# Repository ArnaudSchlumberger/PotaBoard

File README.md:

# PotaBoard

This repository contains all the code, and PCB design files related to PotaBoard, a BLE-powered board kitchen garden.

It comes with capacitive-moisure sensor and BME280 compatibility for temperature and pressure measurements.

Used microcontroller : ATtiny1604 with Arduino Nano UPDI Programmer

BLE module : EMB1061.

All eletronics-related files are in 'Electronics - Extras' folder, and contains:
- Components Datasheets in 'Datasheets' folder
- Kicad project and related libraries in 'Kicad project' folder

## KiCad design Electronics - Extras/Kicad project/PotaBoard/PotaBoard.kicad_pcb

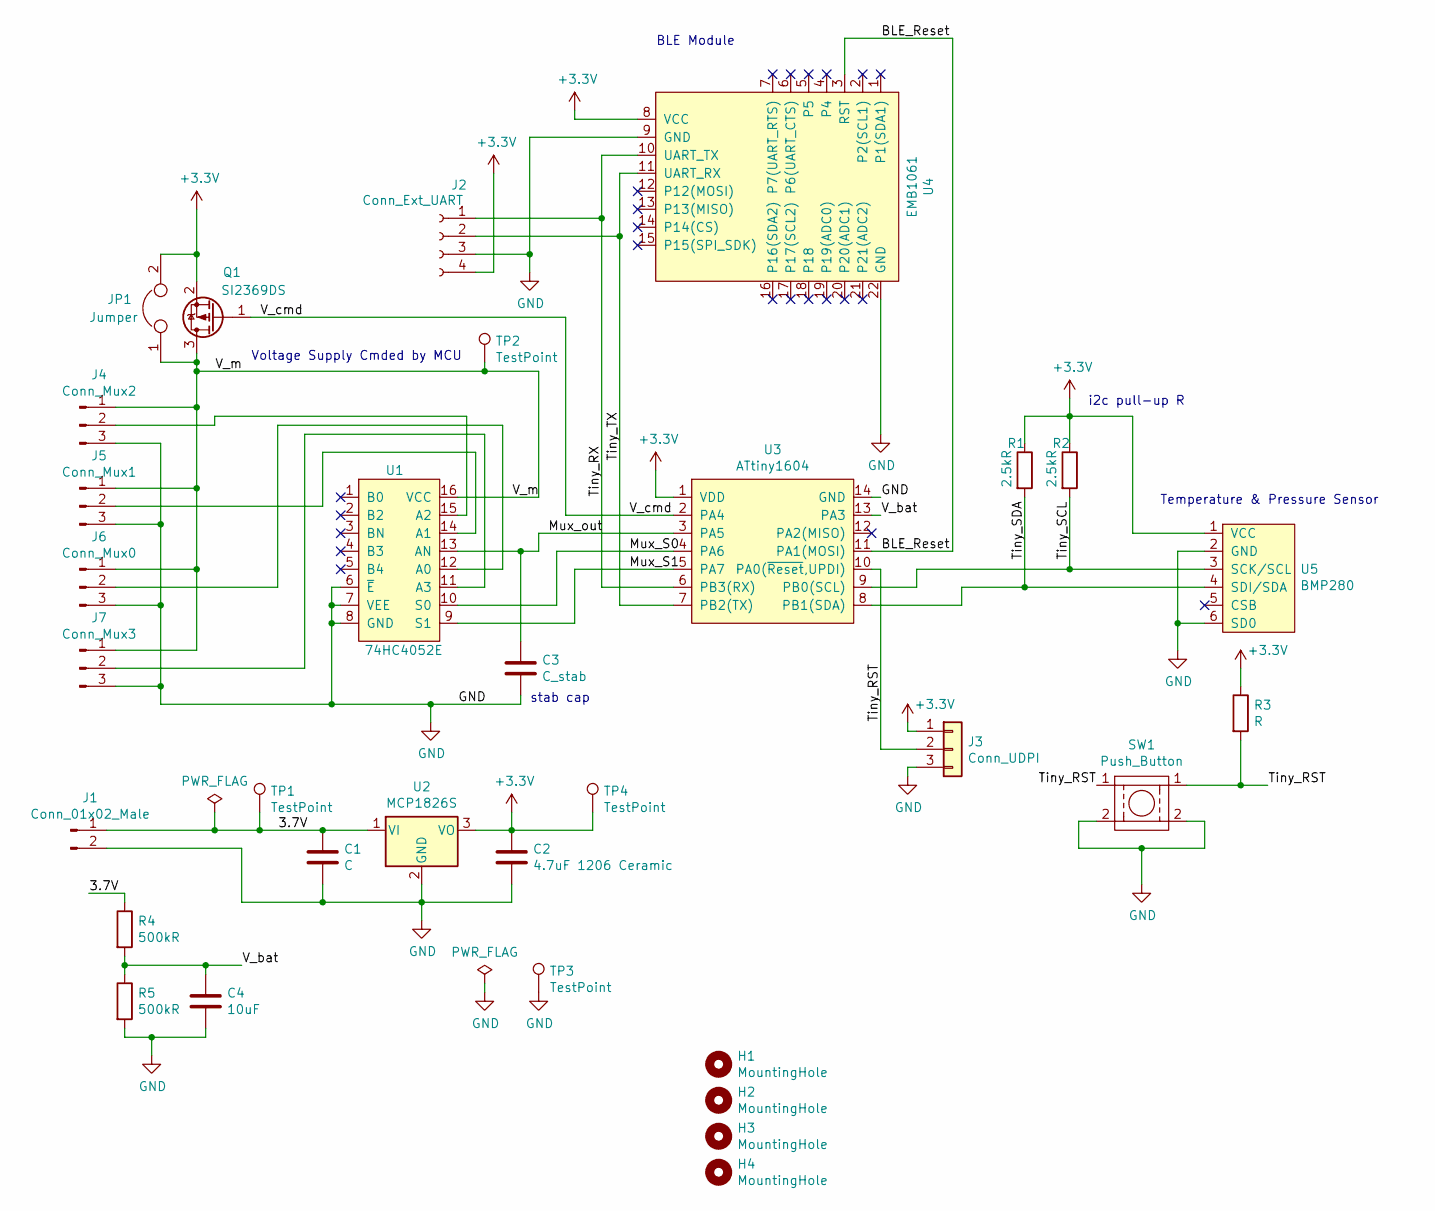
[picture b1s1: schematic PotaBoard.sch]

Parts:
C1: C; C_1206_3216Metric_Pad1.42x1.75mm_HandSolder
C2: 4.7uF 1206 Ceramic; C_1206_3216Metric_Pad1.42x1.75mm_HandSolder
C3: C_stab; C_1206_3216Metric_Pad1.42x1.75mm_HandSolder
C4: 10uF; C_1206_3216Metric_Pad1.42x1.75mm_HandSolder
H1, H2, H3, H4: MountingHole; MountingHole_3.2mm_M3
J1: Conn_01x02_Male; PinHeader_1x02_P2.54mm_Vertical
J2: Conn_Ext_UART; PinHeader_1x04_P2.54mm_Vertical
J3: Conn_UDPI; PinHeader_1x03_P2.54mm_Vertical
J4: Conn_Mux2; PinHeader_1x03_P2.54mm_Vertical
J5: Conn_Mux1; PinHeader_1x03_P2.54mm_Vertical
J6: Conn_Mux0; PinHeader_1x03_P2.54mm_Vertical
J7: Conn_Mux3; PinHeader_1x03_P2.54mm_Vertical
JP1: Jumper; R_1206_3216Metric_Pad1.42x1.75mm_HandSolder
Q1: SI2369DS; SOT-23_Handsoldering
R1, R2: 2.5kR; R_1206_3216Metric_Pad1.42x1.75mm_HandSolder
R3: R; R_1206_3216Metric_Pad1.42x1.75mm_HandSolder
R4, R5: 500kR; R_1206_3216Metric_Pad1.42x1.75mm_HandSolder
SW1: Push_Button; SW_Push_1P1T_NO_6x6mm_H9.5mm
TP1, TP2, TP3, TP4: TestPoint; TestPoint_Pad_D2.0mm
U1: 74HC4052E; DIP-16_W7.62mm
U2: MCP1826S; SOT-223
U3: ATtiny1604; SOIC-14_3.9x8.7mm_P1.27mm
U4: EMB1061
U5: BMP280

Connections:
+3V3: C2.1, J2.4, J3.1, JP1.2, Q1.2 (S), R1.1, R2.1, R3.1, TP4.1, U2.3 (VO), U3.1 (VDD), U4.8 (VCC), U5.1 (VCC)
/3.7V: C1.1, J1.1, R4.1, TP1.1, U2.1 (VI)
/BLE_Reset: U3.11 (PA1(MOSI)), U4.3 (RST)
/Mux_S0: U1.10 (S0), U3.4 (PA6)
/Mux_S1: U1.9 (S1), U3.5 (PA7)
/Mux_out: C3.1, U1.13 (AN), U3.3 (PA5)
/Tiny_RST: J3.2, R3.2, SW1.1, U3.10 (PA0(~Reset~,UPDI))
/Tiny_RX: J2.1, U3.6 (PB3(RX)), U4.10 (UART_TX)
/Tiny_SCL: R2.2, U3.9 (PB0(SCL)), U5.3 (SCK/SCL)
/Tiny_SDA: R1.2, U3.8 (PB1(SDA)), U5.4 (SDI/SDA)
/Tiny_TX: J2.2, U3.7 (PB2(TX)), U4.11 (UART_RX)
/V_bat: C4.1, R4.2, R5.1, U3.13 (PA3)
/V_cmd: Q1.1 (G), U3.2 (PA4)
/V_m: J4.1, J5.1, J6.1, J7.1, JP1.1, Q1.3 (D), TP2.1, U1.16 (VCC)
GND: C1.2, C2.2, C3.2, C4.2, J1.2, J2.3, J3.3, J4.3, J5.3, J6.3, J7.3, R5.2, SW1.2, TP3.1, U1.6 (~E), U1.7 (VEE), U1.8 (GND), U2.2 (GND), U3.14 (GND), U4.9 (GND), U4.22 (GND), U5.2 (GND), U5.6 (SD0)
unnamed: J4.2, U1.15 (A2)
unnamed: J5.2, U1.14 (A1)
unnamed: J6.2, U1.12 (A0)
unnamed: J7.2, U1.11 (A3)

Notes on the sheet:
i2c pull-up R
stab cap
Voltage Supply Cmded by MCU
Temperature & Pressure Sensor
BLE Module

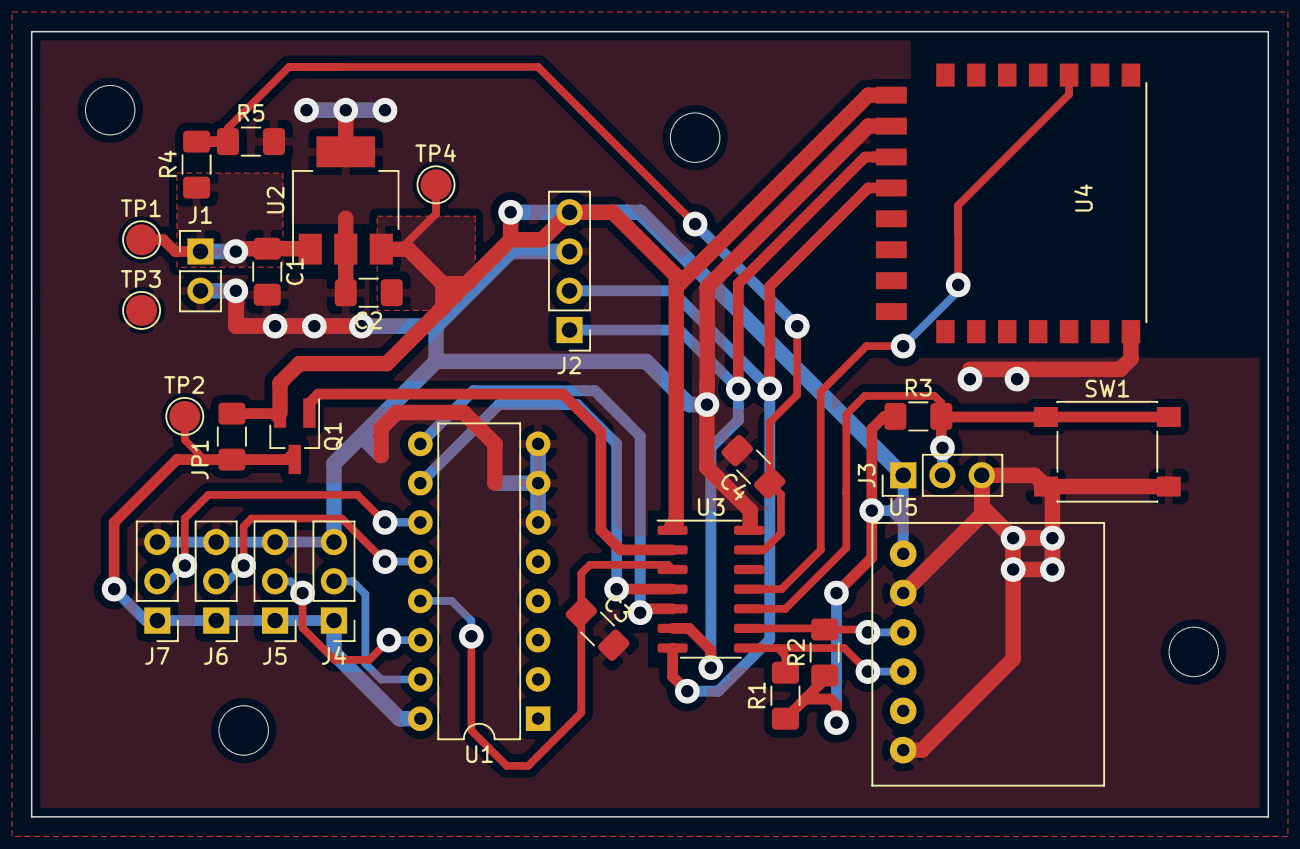
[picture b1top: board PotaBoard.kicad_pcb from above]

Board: 2 copper layers, 80.0 x 50.8 mm, 32 parts (0 on the bottom side), 19 nets.

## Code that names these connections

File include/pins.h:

#ifndef PINS_H
#define PINS_H

#define V_CMD 0 //Output pin to control multiplexer power supply
#define MUX_OUT 1 //Analog input for Mux value reading
#define MUX_SEL_0 2 //Digital output to Mux S0 pin
#define MUX_SEL_1 3 //Digital output to Mux S1 pin
#define BLE_Reset 8 //Digital output to BLE Reset pin
#define V_bat 10 //Analog input to battery voltage (divided by a factor 2)


#endif

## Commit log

2021-02-16 Git setup
2021-02-16 Added README file
2021-02-16 Added BME280 measurement update
2021-02-16 Added references related to PCB design and electronics
2021-02-16 Optimized BME Forced Mode Transition
2021-07-19 Retrait fonctionnalite DUTY CYCLE sur les DI - Mise a jour valeur de resistance AOx
2022-09-18 Battery : modified voltage reading function, added raw ADC reading function. Main : added debug mode, cleaned unused variables, reforged BLE instructions values and overall working principle. Potadat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
